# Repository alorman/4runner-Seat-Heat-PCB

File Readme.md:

# 4Runner Heated Seat Control Board

## Pictures

## Schematic
[Schematic](exports/Schematics/4Runner-seat-heat-rev03-schematic.pdf)

## BOM
[Interactive BOM](https://alorman.github.io/4runner-Seat-Heat-PCB/exports/BOM/ibom.html)

## Gerbers
[Gerber](exports/Gerbers)

## STEP Files
[STEP](exports/STEP/4runner-seat-heat-rev03.step)

## Fab Instructions
| | |
|-------------------|---------------:|
| Height (mm)       | 75             |
| Width (mm)        | 72             |
| Layers            | 2              |
| Thickness (mm)    | 1.6            |
| Solder Mask       | Black          |
| Silkscreen        | White          |
| Copper Thickness  | 1 oz           |
| Min Spacing       | 8/8mil         |
| Min Hole Size     | 8mil           |
| Via Process       | Tented         |
| Surface Treatment | HASL-Lead Free |
| Special Notes     | None           |

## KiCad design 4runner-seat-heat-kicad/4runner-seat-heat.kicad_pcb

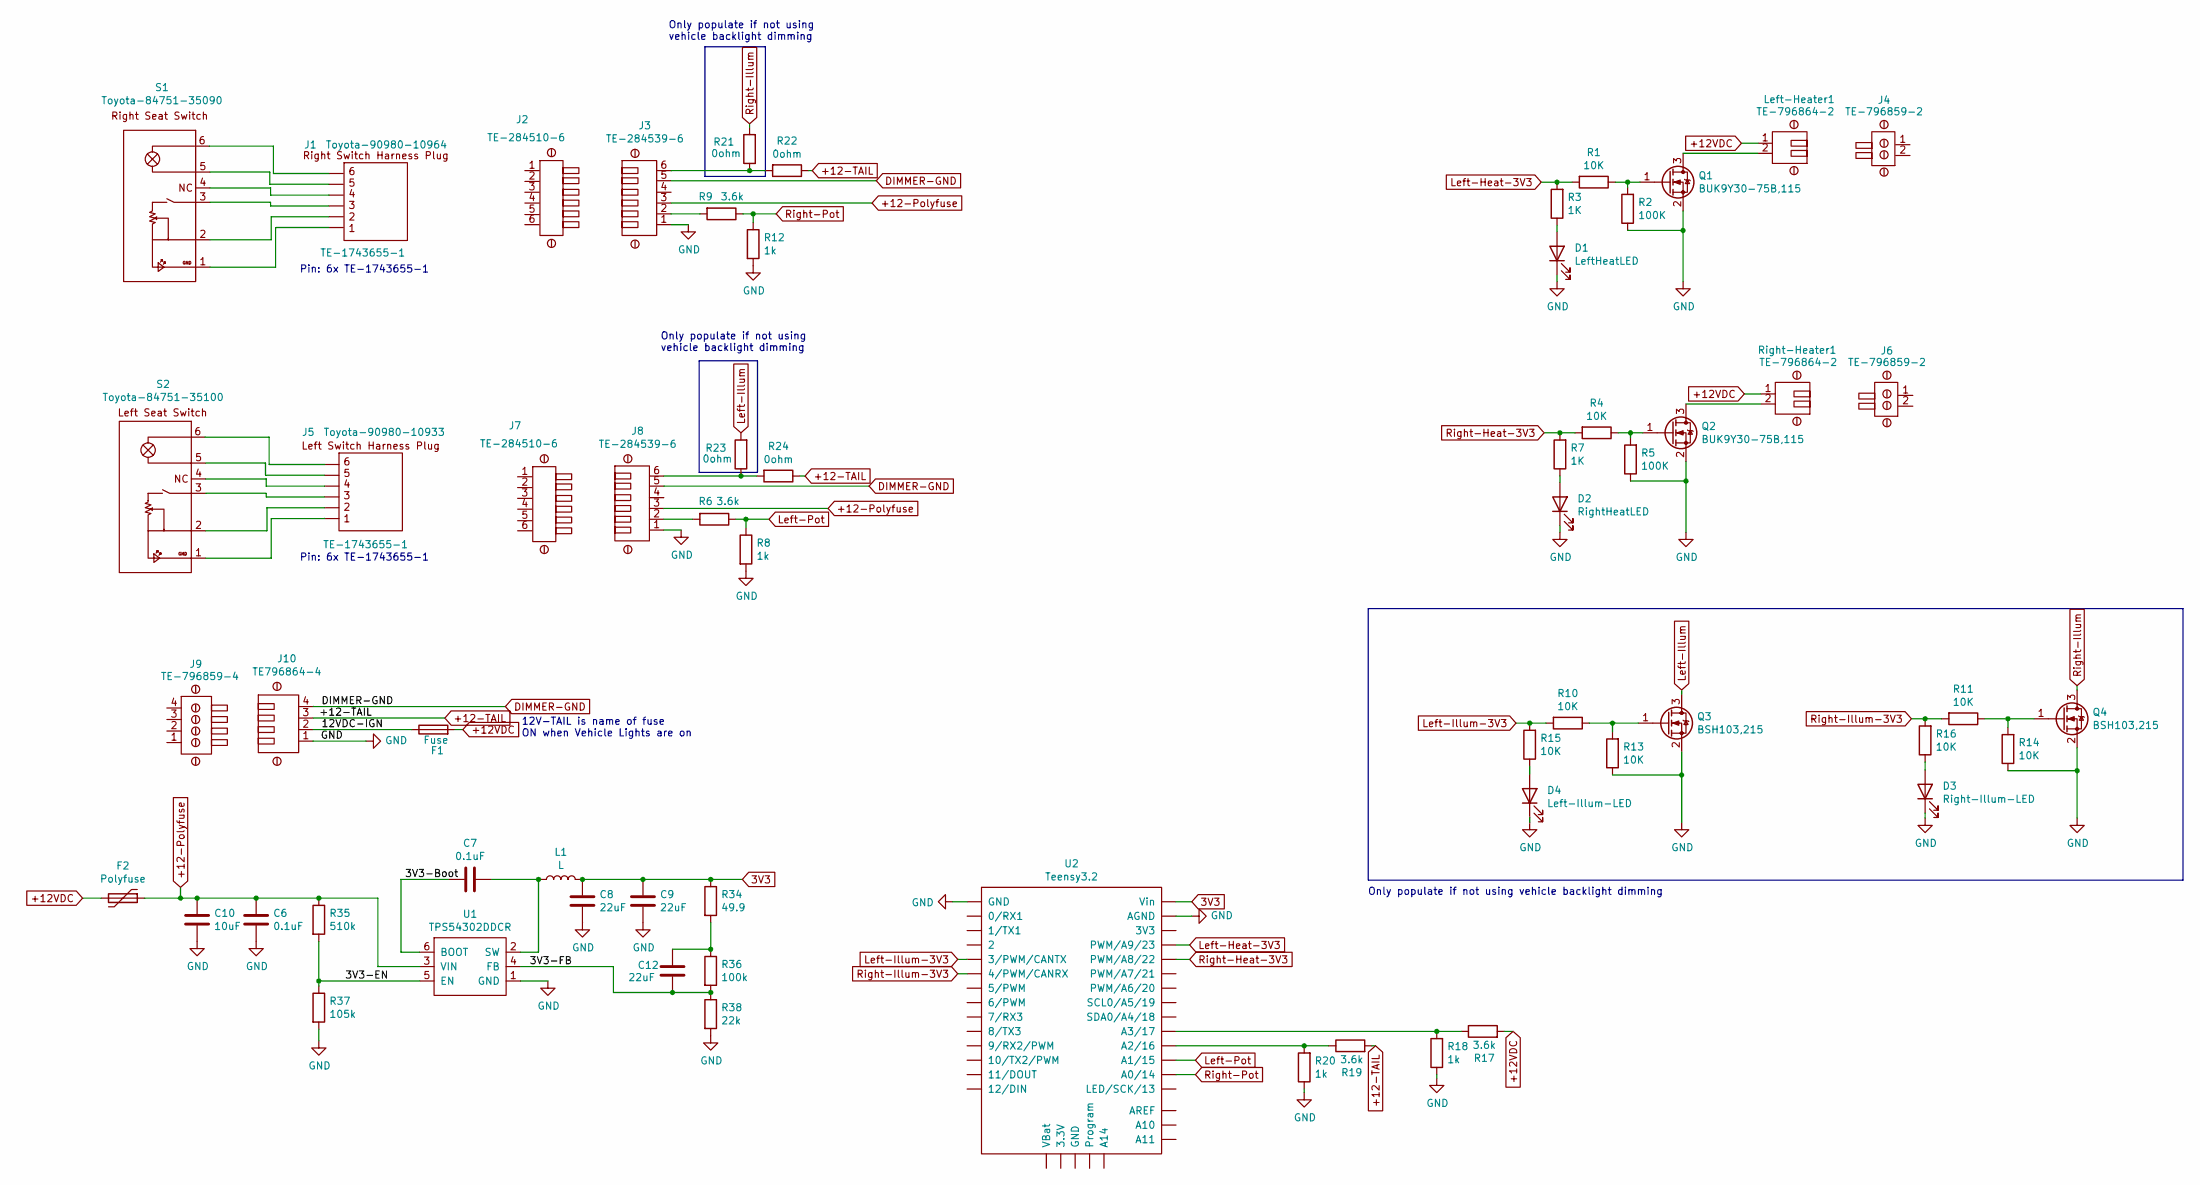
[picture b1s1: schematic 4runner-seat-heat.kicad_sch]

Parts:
C6: 0.1uF; C_1210_3225Metric
C7: 0.1uF; C_0603_1608Metric
C8, C9: 22uF; C_1210_3225Metric
C10: 10uF; C_1210_3225Metric
C12: 22uF; C_0603_1608Metric
D1: LeftHeatLED; Kingbright-APT1608LZGCK
D2: RightHeatLED; Kingbright-APT1608LZGCK
D3: Right-Illum-LED; Kingbright-APT1608LZGCK
D4: Left-Illum-LED; Kingbright-APT1608LZGCK
F1: Fuse; Keystone-3587-20
F2: Polyfuse; Fuse_0603_1608Metric
J1: Toyota-90980-10964; DNP-Mechanical
J2: TE-284510-6; dev-empty-footprint
J3, J8: TE-284539-6
J4, J6: TE-796859-2; DNP-Mechanical
J5: Toyota-90980-10933; DNP-Mechanical
J7: TE-284510-6; DNP-Mechanical
J9: TE-796859-4; DNP-Mechanical
J10: TE796864-4; TE-796864-4
L1: L; Wurth-7447714068
Left-Heater1: TE-796864-2
Pin1: TE-1743655-1; dev-empty-footprint
Pin2, Pin3, Pin4, Pin5, Pin6, Pin7, Pin8, Pin9, Pin10, Pin11, Pin12: TE-1743655-1; DNP-Mechanical
Q1, Q2: BUK9Y30-75B,115; BUK9Y30-75B,115-SOT669
Q3, Q4: BSH103,215
R1, R4, R10, R11, R13, R14, R15, R16: 10K; R_0603_1608Metric
R2, R5: 100K; R_0603_1608Metric
R3, R7: 1K; R_0603_1608Metric
R6, R9, R17, R19: 3.6k; R_0603_1608Metric
R8, R12, R18, R20: 1k; R_0603_1608Metric
R21, R22, R23, R24: 0ohm; R_0603_1608Metric
R34: 49.9; R_0603_1608Metric
R35: 510k; R_0603_1608Metric
R36: 100k; R_0603_1608Metric
R37: 105k; R_0603_1608Metric
R38: 22k; R_0603_1608Metric_Pad0.98x0.95mm_HandSolder
Right-Heater1: TE-796864-2
S1: Toyota-84751-35090; DNP-Mechanical
S2: Toyota-84751-35100; DNP-Mechanical
U1: TPS54302DDCR
U2: Teensy3.2; Teensy30_31_32_LC

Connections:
3V3: C8.2, C9.2, L1.2, R34.1, U2.Vin
+12-Polyfuse: C6.1, C10.1, F2.1, J3.3, J8.3, R35.1, U1.3 (VIN)
+12-TAIL: J9.3, J10.3, R19.2, R22.1, R24.1
+12VDC: F1.2, F2.2, Left-Heater1.1, R17.2, Right-Heater1.1
/3V3-Boot: C7.2, U1.6 (BOOT)
/3V3-EN: R35.2, R37.1, U1.5 (EN)
/3V3-FB: C12.1, R36.2, R38.1, U1.4 (FB)
/12VDC-IGN: F1.1, J9.2, J10.2
DIMMER-GND: J3.5, J8.5, J9.4, J10.4
GND: C6.2, C8.1, C9.1, C10.2, D1.1 (K), D2.1 (K), D3.1 (K), D4.1 (K), J3.1, J8.1, J9.1, J10.1, Q1.2 (S), Q2.2 (S), Q3.2 (S), Q4.2 (S), R2.1, R5.1, R8.2, R12.2, R13.1, R14.1, R18.1, R20.1, R37.2, R38.2, U1.1 (GND), U2.AGND, U2.GND
Left-Heat-3V3: R1.2, R3.2, U2.23 (PWM/A9/23)
Left-Illum: Q3.3 (D), R23.2
Left-Illum-3V3: R10.2, R15.2, U2.3 (3/PWM/CANTX)
Left-Pot: R6.1, R8.1, U2.15 (A1/15)
unnamed: C7.1, L1.1, U1.2 (SW)
unnamed: C12.2, R34.2, R36.1
unnamed: D1.2 (A), R3.1
unnamed: D2.2 (A), R7.1
unnamed: D3.2 (A), R16.1
unnamed: D4.2 (A), R15.1
unnamed: J3.2, R9.2
unnamed: J3.6, R21.1, R22.2
unnamed: J8.2, R6.2
unnamed: J8.6, R23.1, R24.2
unnamed: Left-Heater1.2, Q1.3 (D)
unnamed: Pin1.1, S1.6
unnamed: Pin2.1, S1.5
unnamed: Pin3.1, S1.4
unnamed: Pin4.1, S1.3
unnamed: Pin5.1, S1.2
unnamed: Pin6.1, S1.1
unnamed: Pin7.1, S2.6
unnamed: Pin8.1, S2.5
unnamed: Pin9.1, S2.4
unnamed: Pin10.1, S2.3
unnamed: Pin11.1, S2.2
unnamed: Pin12.1, S2.1
unnamed: Q1.1 (G), R1.1, R2.2
unnamed: Q2.1 (G), R4.1, R5.2
unnamed: Q2.3 (D), Right-Heater1.2
unnamed: Q3.1 (G), R10.1, R13.2
unnamed: Q4.1 (G), R11.1, R14.2
unnamed: R19.1, R20.2, U2.16 (A2/16)
Right-Heat-3V3: R4.2, R7.2, U2.22 (PWM/A8/22)
Right-Illum: Q4.3 (D), R21.2
Right-Illum-3V3: R11.2, R16.2, U2.4 (4/PWM/CANRX)
Right-Pot: R9.1, R12.1, U2.14 (A0/14)

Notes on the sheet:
Pin: 6x TE-1743655-1
Only populate if not using vehicle backlight dimming
Only populate if not using vehicle backlight dimming
12V-TAIL is name of fuse ON when Vehicle Lights are on

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
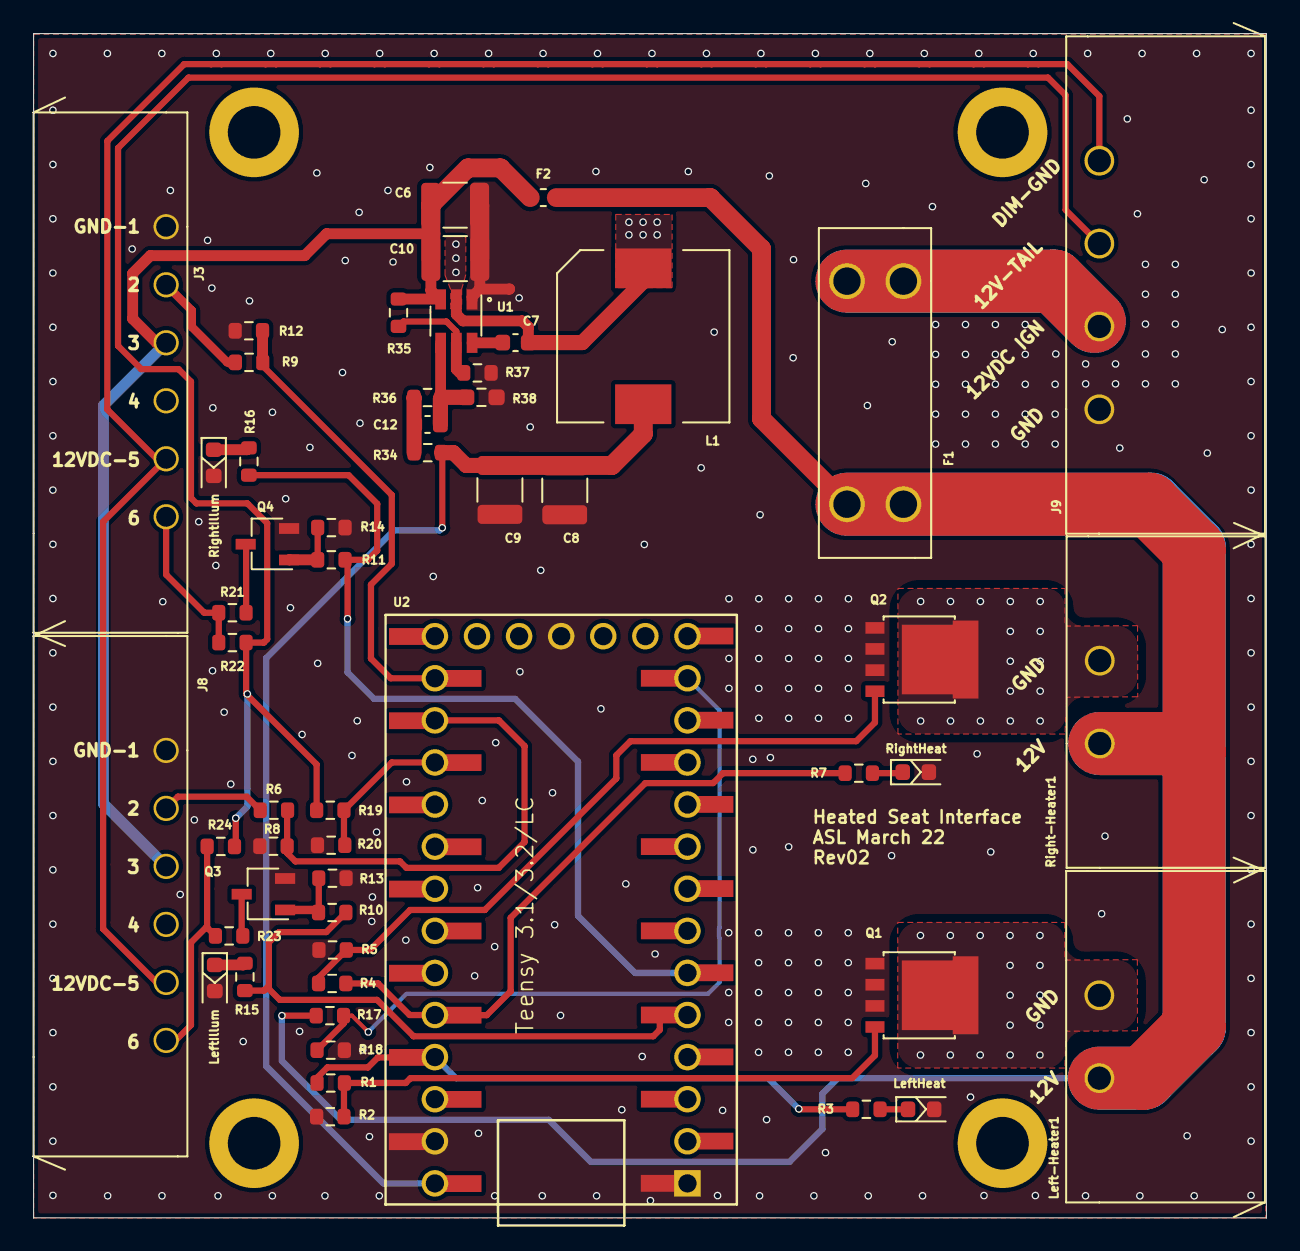
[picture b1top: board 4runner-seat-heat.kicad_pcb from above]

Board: 2 copper layers, 74.4 x 71.5 mm, 71 parts (0 on the bottom side), 47 nets.

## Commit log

2021-12-26 initial commit after conversion from kicad
2021-12-26 update table
2021-12-29 spelling
2022-02-19 update to add pin part number to schematics
2022-02-28 change connector to 4 pin, add circuitry to allow backlight to be driven from tail relay
2022-03-12 add moutning holes, export of Gerbers for rev02 and step files
2022-03-13 update pcb art, re-gerber, edit readme, ready for fab
2022-03-13 all jlc zipped gerber
2022-03-13 rev02 schematic fix
2022-03-19 Re-sort step and schematic files
2022-03-19 refresh submodules
2022-03-20 fix ibom, add mcmaster parts to BOM
2022-03-20 update gerbers to check submodule diffing
2022-12-24 silkscreen and small layout changes
2022-12-24 push all versions to rev03
2022-12-24 pdf minor change
2024-06-30 rework broken pcb file, bump kicad version to 7, update readme
2024-07-06 fix broken landing page links
2024-07-18 fix bad link
